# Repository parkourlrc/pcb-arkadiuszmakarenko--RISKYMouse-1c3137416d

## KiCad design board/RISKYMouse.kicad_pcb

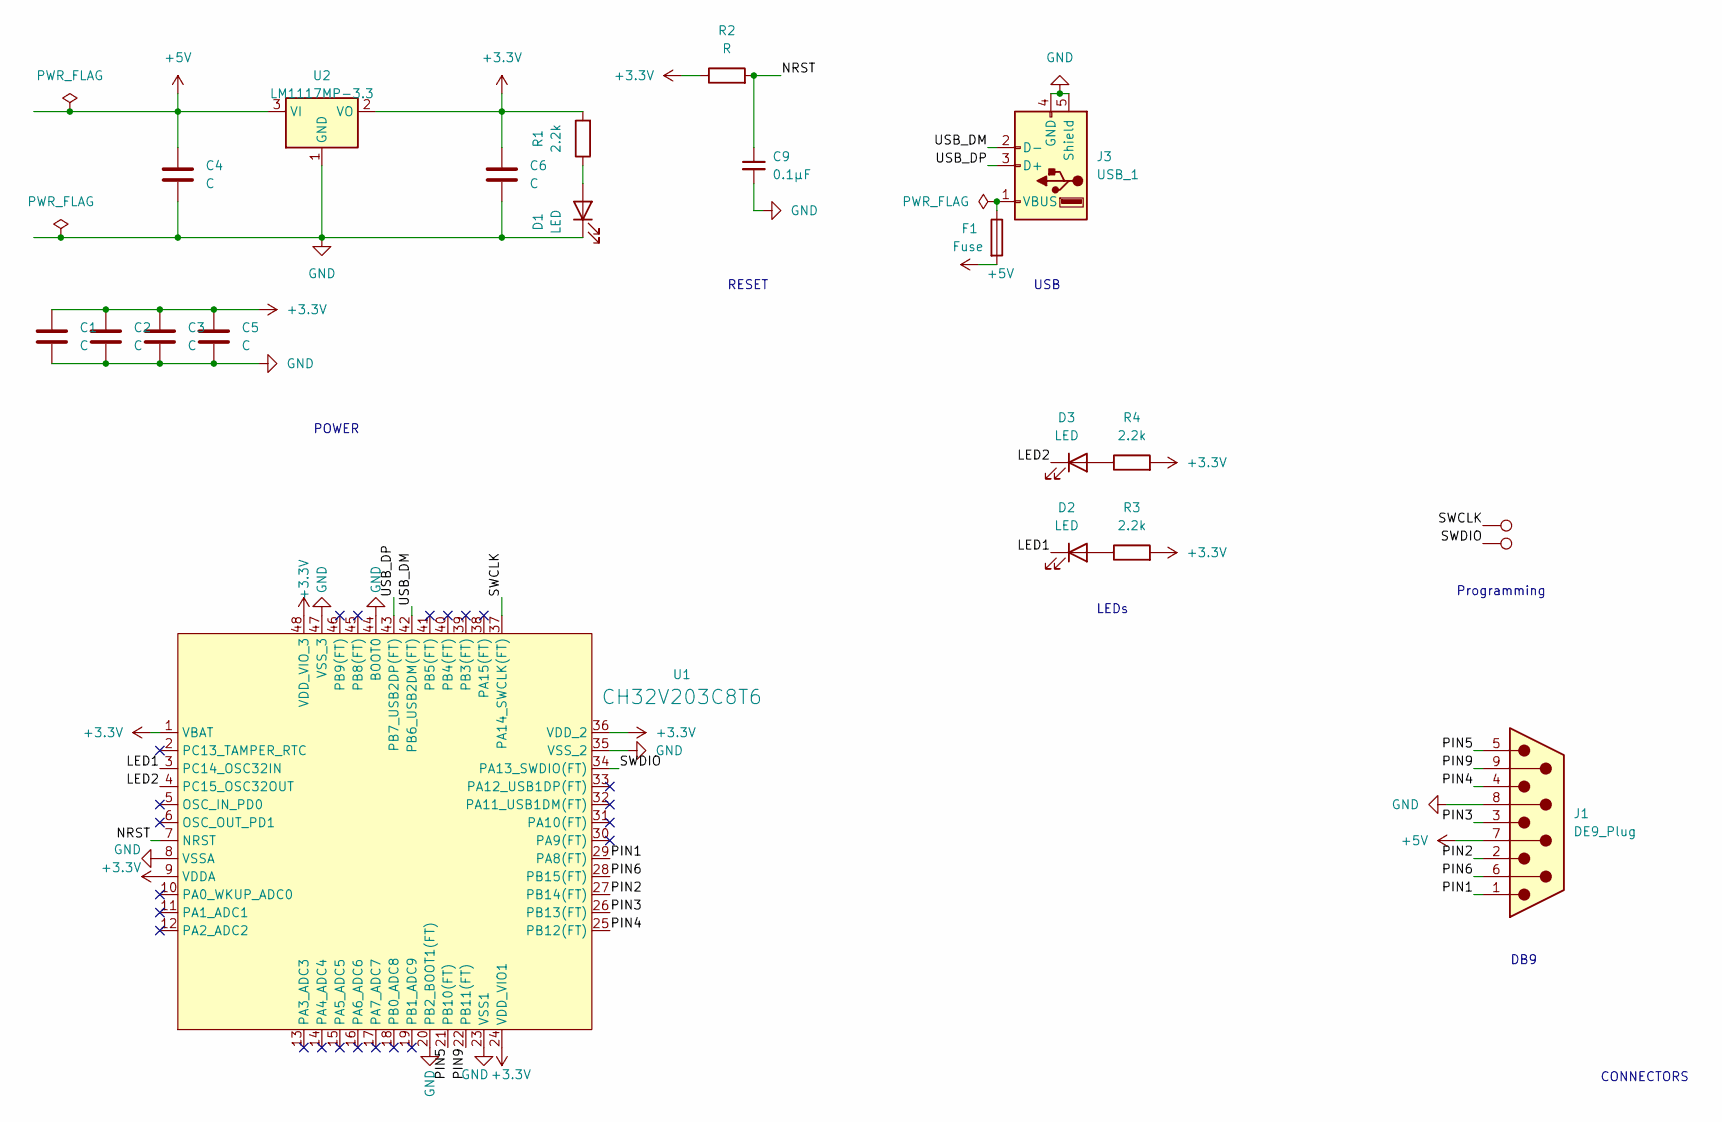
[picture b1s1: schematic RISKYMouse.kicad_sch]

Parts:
C1, C2, C3, C4, C5, C6: C; C_0603_1608Metric_Pad1.08x0.95mm_HandSolder
C9: 0.1μF; C_0603_1608Metric_Pad1.08x0.95mm_HandSolder; LCSC C14663
D1, D2, D3: LED; LED_0805_2012Metric_Pad1.15x1.40mm_HandSolder
F1: Fuse; Fuse_1206_3216Metric_Pad1.42x1.75mm_HandSolder
J1: DE9_Plug; DSUB-9_Socket_EdgeMount_P2.77mm
J3: USB_1; USB_A_Connfly_DS1095
R1, R3, R4: 2.2k; R_0603_1608Metric_Pad0.98x0.95mm_HandSolder
R2: R; R_0603_1608Metric_Pad0.98x0.95mm_HandSolder
TP1, TP2: TestPoint; TestPoint_Pad_1.0x1.0mm
U1: CH32V203C8T6; LQFP-48_7x7mm_P0.5mm
U2: LM1117MP-3.3; SOT-89-3

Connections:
+3.3V: C1.1, C2.1, C3.1, C5.1, C6.1, R1.2, R2.1, R3.2, R4.2, U1.1 (VBAT), U1.9 (VDDA), U1.24 (VDD_VIO1), U1.36 (VDD_2), U1.48 (VDD_VIO_3), U2.2 (VO)
+5V: C4.1, F1.2, J1.7, U2.3 (VI)
/LED1: D2.1 (K), U1.3 (PC14_OSC32IN)
/LED2: D3.1 (K), U1.4 (PC15_OSC32OUT)
/NRST: C9.1, R2.2, U1.7 (NRST)
/PIN1: J1.1, U1.29 (PA8(FT))
/PIN2: J1.2, U1.27 (PB14(FT))
/PIN3: J1.3, U1.26 (PB13(FT))
/PIN4: J1.4, U1.25 (PB12(FT))
/PIN5: J1.5, U1.21 (PB10(FT))
/PIN6: J1.6, U1.28 (PB15(FT))
/PIN9: J1.9, U1.22 (PB11(FT))
/SWCLK: TP1.1 (1_1), U1.37 (PA14_SWCLK(FT))
/SWDIO: TP2.1 (1_1), U1.34 (PA13_SWDIO(FT))
/USB_DM: J3.2 (D-), U1.42 (PB6_USB2DM(FT))
/USB_DP: J3.3 (D+), U1.43 (PB7_USB2DP(FT))
GND: C1.2, C2.2, C3.2, C4.2, C5.2, C6.2, C9.2, D1.1 (K), J1.8, J3.4 (GND), J3.5 (Shield), U1.8 (VSSA), U1.20 (PB2_BOOT1(FT)), U1.23 (VSS1), U1.35 (VSS_2), U1.44 (BOOT0), U1.47 (VSS_3), U2.1 (GND)
unnamed: D1.2 (A), R1.1
unnamed: D2.2 (A), R3.1
unnamed: D3.2 (A), R4.1
unnamed: F1.1, J3.1 (VBUS)

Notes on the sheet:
USB
LEDs
Programming
POWER
CONNECTORS
DB9
RESET

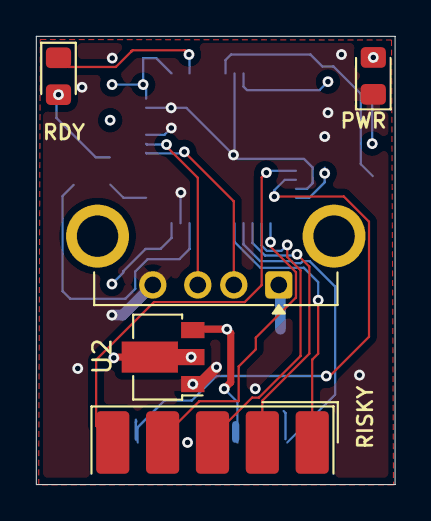
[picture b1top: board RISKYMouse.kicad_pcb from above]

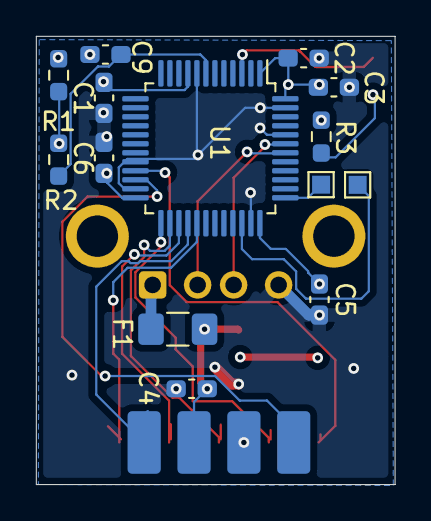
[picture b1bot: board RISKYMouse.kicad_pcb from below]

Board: 4 copper layers, 19.9 x 24.9 mm, 19 parts (14 on the bottom side), 19 nets.

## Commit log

2026-06-19 New PCB - minified
